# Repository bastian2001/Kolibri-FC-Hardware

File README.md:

# RP2350 Flight Controller for FPV

This is the hardware part of the Kolibri Flight Controller. Currently there are two versions: A 30mm (V0.5) and a 20mm (V0.6) FC. They are both pretty similar in terms of features, and mostly differ in their form factor and ease of soldering, but also featurewise, they are slightly different. They both feature:

-   3-8S input voltage
-   RP2350 microcontroller
-   2.4GHz ELRS onboard
-   5V 2.5A, 10V 2.5A buck converters
-   Analog character based OSD similar to Betaflight/iNav
-   Barometer (STM LPS22HB)
-   Speaker driver up to VBat

They differ slightly:

-   Gyro: BMI270 (30mm), ICM-42688-P with separate LDO (20mm)
-   ELRS: Gemini with PA/LNA (30mm), only one antenna with no PA/LNA (20mm)
-   Blackbox: SD slot (30mm), 256MiB flash chip (20mm)
-   20mm has a switchable 10V rail, 30mm uses that pin for a current sensor

While the 30mm FC works really well, the 20mm FC is just ordered and completely untested. While most features are a size decision, I will probably phase out the BMI270 and switch over to the ICM-42688-P, and I'd count a switchable 10V rail as more important than a current sensor, so as long as a 2350 is used, I will probably do that in the future, too. An RP235xB (only feasible on 30mm FC) has more pins though and might offer more features down the line, too.

The firmware and configurator can be found [here](https://github.com/bastian2001/Kolibri-FC).

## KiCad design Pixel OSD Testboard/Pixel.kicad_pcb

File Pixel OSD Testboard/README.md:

# Goal of this board

I want to implement a pixel OSD in some future FC version. Because I am very unsure about how PAL/NTSC work, I want to test all of the hardware on a separate, cheap and easily debuggable, board first. It has a bunch of components that I want to remove later on, and that are just for debugging (thus making it larger than it needs to be). Furthermore, some of the hardware is chosen purely because I have it laying around (e.g. RP2040 instead of RP2350), so I get rid of old stock.

Pixel OSD will have multiple advantages

-   Drawing graphs and free shapes
-   varying font size and grid
-   cheaper
-   shades of grey (hopefully)
-   optional: remove grey, save one pin compared to MAX (hopefully)

This board is only a proof of concept. I'll try to put it into my quad during flight, but in the end it will be implemented on the main FC. Thus, it will likely only support a character based OSD, so it doesn't require a whole rewrite of the FC firmware for now: The interface is Serial/UART with MSP Displayport. Yes, hopefully this can give us a higher character count on regular analog video (to some extent, because the resolution is already close to its limit)

## Stuff that will be removed later on

-   Maybe I can buffer a bit less: 1-2 op amp channels could go?
-   Are all 100nF caps needed?
-   video LPF on LM1881 input?
-   Virtual white and the white selector: White should just come from the peak detector
-   Some components for lines like VSync: I want to use only composite sync
-   RP2040/LDO/LED/USB: Will be integrated into main RP2350 instead of MAX7456E

## How it works

How the hardware works is commented on the sheet.

The software will use PIO to detect sync pulses, then use DMA to feed a pixel buffer into the PIO which then outputs the data, timed correctly. PIO has the advantage of not needing super precise interrupt timing, because the coprocessor is very precise time-wise by definition.

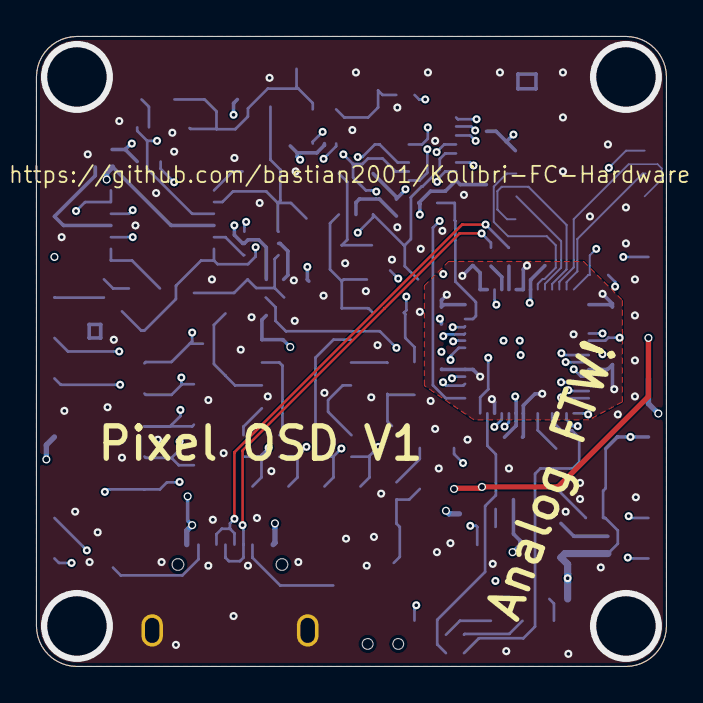
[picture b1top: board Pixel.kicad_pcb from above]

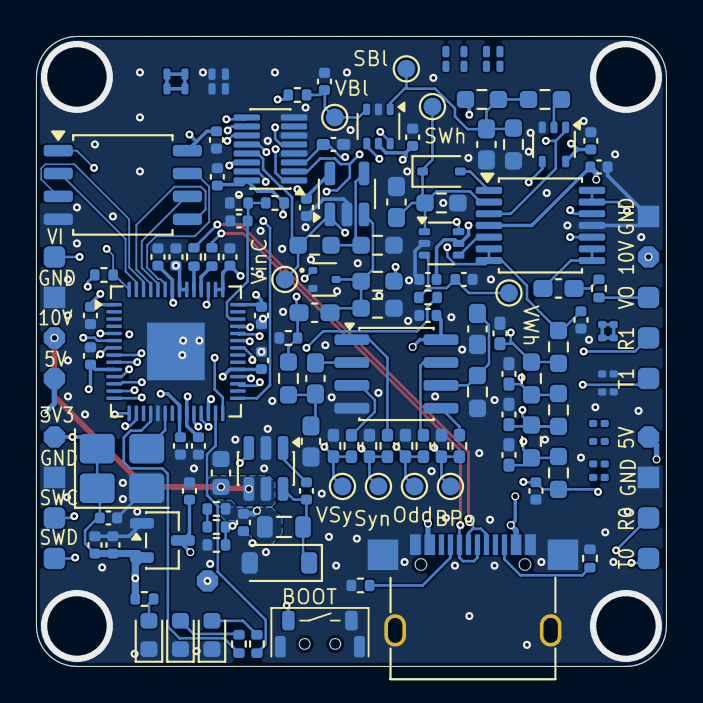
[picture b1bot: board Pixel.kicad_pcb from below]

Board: 6 copper layers, 35.0 x 35.0 mm, 145 parts (145 on the bottom side), 79 nets.

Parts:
C1, C2, C3, C4, C5, C6, C7, C8, C9, C10, C14, C15, C16, C19, C20, C22, C28, C45, C46, C54, C56, C57: 100n; C_0402_1005Metric
C11, C12: 100n; C_0603_1608Metric_Pad1.08x0.95mm_HandSolder
C13: 510p; C_0603_1608Metric_Pad1.08x0.95mm_HandSolder
C17, C18, C52: 10u; C_0603_1608Metric_Pad1.08x0.95mm_HandSolder
C21, C49, C50, C55: 1u; C_0402_1005Metric
C23: 10p; C_0402_1005Metric_Pad0.74x0.62mm_HandSolder
C24, C25, C26, C27: 100n; C_0402_1005Metric_Pad0.74x0.62mm_HandSolder
C29, C30, C31, C32, C33, C34, C35, C36: C; C_0201_0603Metric
C37, C38, C39, C40, C41, C42, C43, C44: C; C_0201_0603Metric_Pad0.64x0.40mm_HandSolder
C47, C51: 10u; C_0402_1005Metric
C48: 10u; C_0603_1608Metric
C53: 1u; C_0603_1608Metric_Pad1.08x0.95mm_HandSolder
D1: 1N4148WS; D_SOD-323
D2: yellow; LED_0603_1608Metric
D3: green; LED_0603_1608Metric
D4: red; LED_0603_1608Metric
D5: SL16; D_SOD-123
J1: USB_C_Receptacle_USB2.0_16P; USB-C SMD+THT
L1: 10u; L_0805_2012Metric
P1, P2, P3, P4, P5, P6, P7, P8: Solder_Pad_rounded
P9, P10, P11, P12, P13, P14: Solder_Pad_octa
P15, P16, P17, P18: Solder_Pad_rect
Q1: 2SK3019; SOT-523
R1, R2: 5.1k; R_0402_1005Metric
R3, R4: 27; R_0402_1005Metric
R5: 680; R_0603_1608Metric_Pad0.98x0.95mm_HandSolder
R6: 620; R_0603_1608Metric_Pad0.98x0.95mm_HandSolder
R7, R9, R11, R13: 33k; R_0402_1005Metric_Pad0.72x0.64mm_HandSolder
R8, R10, R12, R14: 100k; R_0402_1005Metric_Pad0.72x0.64mm_HandSolder
R15, R39: 1k; R_0402_1005Metric
R16, R27, R36: 10k; R_0402_1005Metric
R18: 100; R_0603_1608Metric_Pad0.98x0.95mm_HandSolder
R19, R20: 100k; R_0603_1608Metric_Pad0.98x0.95mm_HandSolder
R22, R23, R24, R25, R26, R43, R44: 1k; R_0603_1608Metric_Pad0.98x0.95mm_HandSolder
R28, R29: 75; R_0402_1005Metric
R32, R33: 100k; R_0402_1005Metric
R34: 47k; R_0402_1005Metric
R35: 15k; R_0402_1005Metric
R37, R38: 470; R_0402_1005Metric
R40: 1M; R_0603_1608Metric_Pad0.98x0.95mm_HandSolder
R41: 2.2M; R_0603_1608Metric_Pad0.98x0.95mm_HandSolder
R42: 390k; R_0603_1608Metric_Pad0.98x0.95mm_HandSolder
SW1: Button C530669
TP1, TP2, TP3, TP4, TP5, TP6, TP8, TP9, TP10: TestPoint_Probe; TestPoint_Pad_D1.0mm
U1: RP2040; QFN-56-1EP_7x7mm_P0.4mm_EP3.2x3.2mm
U2: LM1881; SOIC-8_3.9x4.9mm_P1.27mm
U3: W25Q16JVSS; SOIC-8_5.3x5.3mm_P1.27mm
U4: Opamp_Quad; TSSOP-14_4.4x5mm_P0.65mm
U5: 74LVC1G66; SOT-353_SC-70-5
U6, U10: FSA3157P6X; SOT-363_SC-70-6
U7: TMUX1308DYY; Texas_DYY0016A_TSOT-23-16_2x4.2mm_P0.5mm
U8: LGS5145; SOT-23-6
U9: C19631737; SOT-23-3
U11: OPA188xxDBV; TSOT-23-5
Y1: ASE-xxxMHz; Oscillator_SMD_Abracon_ASE-4Pin_3.2x2.5mm_HandSoldering

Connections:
+1V1: C8.1, C9.1, U1.23 (DVDD), U1.45 (VREG_VOUT), U1.50 (DVDD)
+3V3: C1.1, C2.1, C3.1, C4.1, C5.1, C6.1, C7.1, C10.1, C15.1, C22.1, C45.1, C50.1, C51.1, C56.1, C57.1, P9.1, P11.1, R32.1, R39.1, R40.1, R41.1, U1.1 (IOVDD), U1.10 (IOVDD), U1.22 (IOVDD), U1.26 (RUN), U1.33 (IOVDD), U1.42 (IOVDD), U1.43 (ADC_AVDD), U1.44 (VREG_IN), U1.48 (USB_VDD), U1.49 (IOVDD), U3.8 (VCC), U5.5 (VCC), U6.5 (V+), U7.16 (V_{CC}), U9.2 (VO), U10.5 (V+), Y1.1 (EN), Y1.4 (Vdd)
+5V: C14.1, C16.1, C47.1, C49.1, C54.1, J1.A4 (VBUS), J1.A9 (VBUS), J1.B4 (VBUS), J1.B9 (VBUS), L1.2, P10.1, P12.1, R34.1, U2.8 (VCC), U4.4 (V+), U9.3 (VI), U11.5 (V+)
+10V: C48.1, P13.1, P14.1, U8.4 (EN), U8.5 (VIN)
/BACK_PORCH: R11.2, R12.1, TP3.1, U1.13 (GPIO10)
/BLACK_ADC: C19.1, R26.2, U1.39 (GPIO27_ADC1), U4.13 (-), U4.14, U7.14 (Y1)
/BLACK_CHG: U1.12 (GPIO9), U5.4
/BLACK_SAH: C18.1, R18.2, R20.1, R40.2, TP8.1, U10.1
/BLACK_SELECT: U1.28 (GPIO17), U10.6
/COMPOSITE_SYNC: R7.2, R8.1, TP1.1, U1.5 (GPIO3)
/GREY1: C27.1, R25.2, R26.1, U7.15 (Y2)
/GREY2: C26.1, R24.2, R25.1, U7.12 (Y3)
/GREY3: C25.1, R23.2, R24.1, U7.1 (Y4)
/GREY4: C24.1, R22.2, R23.1, U7.5 (Y5)
/LED1: R38.1, U1.27 (GPIO16)
/LED2: R37.1, U1.18 (GPIO15)
/ODD_FRAME: R13.2, R14.1, TP4.1, U1.7 (GPIO5)
/RX0: P4.1, U1.16 (GPIO13)
/RX1: P8.1, U1.32 (GPIO21)
/SWCLK: P5.1, U1.24 (SWCLK)
/SWDIO: P6.1, U1.25 (SWD)
/SYNC_CLAMP: Q1.1 (G), U1.14 (GPIO11)
/TEST_ADC: C28.1, R32.2, R33.1, U1.40 (GPIO28_ADC2)
/TX0: P3.1, U1.15 (GPIO12)
/TX1: P7.1, U1.31 (GPIO20)
/USBD+: R4.2, U1.47 (USB_DP)
/USBD-: R3.2, U1.46 (USB_DM)
/VBLACK_PWM: R16.1, U1.29 (GPIO18)
/VIDEO_IN: C53.1, P1.1, R6.1, R28.1
/VIDEO_IN_CLAMP: R43.1, TP9.1, U4.3 (+), U5.1, U7.13 (Y0), U11.1
/VIDEO_OUT: P2.1, R29.2
/VSEL0: U1.8 (GPIO6), U7.11 (S0)
/VSEL1: U1.9 (GPIO7), U7.10 (S1)
/VSEL2: U1.11 (GPIO8), U7.9 (S2)
/VSYNC: R9.2, R10.1, TP2.1, U1.6 (GPIO4)
/VWHITE_PWM: R27.1, U1.36 (GPIO24)
/WHITE_ADC: C20.1, R22.1, U1.38 (GPIO26_ADC0), U4.6 (-), U4.7, U7.2 (Y6)
/WHITE_SAH: C17.1, D1.1 (K), R19.1, TP5.1, U4.2 (-), U6.1
/WHITE_SELECT: U1.37 (GPIO25), U6.6
GND: C1.2, C2.2, C3.2, C4.2, C5.2, C6.2, C7.2, C8.2, C9.2, C10.2, C11.2, C13.1, C14.2, C15.2, C16.2, C17.2, C18.2, C19.2, C20.2, C21.2, C22.2, C23.2, C24.2, C25.2, C26.2, C27.2, C28.2, C33.1, C33.2, C34.1, C34.2, C41.1, C41.2, C42.1, C42.2, C45.2, C47.2, C48.2, C49.2, C50.2, C51.2, C54.2, C55.2, C56.2, C57.2, D2.1 (K), D3.1 (K), D4.1 (K), D5.2 (A), J1.A1 (GND), J1.A12 (GND), J1.B1 (GND), J1.B12 (GND), J1.S1 (SHIELD), P15.1, P16.1, P17.1, P18.1, Q1.2 (S), R1.2, R2.2, R5.2, R8.2, R10.2, R12.2, R14.2, R19.2, R20.2, R28.2, R33.2, R36.2, R42.2, R44.2, SW1.2, SW1.3 (MP), SW1.4 (MP), U1.19 (TESTEN), U1.57 (GND), U2.4 (GND), U3.4 (GND), U4.11 (V-), U5.3 (GND), U6.2 (GND), U7.4 (Y7), U7.6 (~E), U7.8 (GND), U8.2 (GND), U9.1 (GND), U10.2 (GND), U11.2 (V-), Y1.2 (GND)
unnamed: C12.1, C13.2, R6.2
unnamed: C21.1, R27.2, TP6.1, U6.3
unnamed: C35.1, C35.2, C36.1, C36.2
unnamed: C43.1, C43.2, C44.1, C44.2
unnamed: C52.2, R29.1
unnamed: C55.1, R16.2, TP10.1, U10.3
unnamed: D1.2 (A), U4.1
unnamed: D2.2 (A), R38.2
unnamed: D3.2 (A), R37.2
unnamed: D4.2 (A), R39.2
unnamed: C46.1, D5.1 (K), L1.1, U8.6 (SW)
unnamed: J1.A5 (CC1), R1.1
unnamed: J1.B5 (CC2), R2.1
unnamed: J1.A6 (D+), J1.B6 (D+), R4.1
unnamed: J1.A7 (D-), J1.B7 (D-), R3.1
unnamed: C53.2, Q1.3 (D), R41.2, R42.1, U11.3 (+)
unnamed: R15.1, SW1.1
unnamed: R18.1, U5.2
unnamed: R34.2, R35.1
unnamed: U1.52 (QSPI_SCLK), U3.6 (CLK)
unnamed: U1.53 (QSPI_SD0), U3.5 (DI/IO_{0})
unnamed: U1.55 (QSPI_SD1), U3.2 (DO/IO_{1})
unnamed: U1.54 (QSPI_SD2), U3.3 (~WP/IO_{2})
unnamed: U1.51 (QSPI_SD3), U3.7 (~HOLD/~RESET/IO_{3})
unnamed: R15.2, U1.56 (QSPI_SS), U3.1 (~CS)
unnamed: U1.20 (XIN), Y1.3 (OUT)
unnamed: R11.1, U2.5 (BPOUT)
unnamed: R7.1, U2.1 (CSOUT)
unnamed: C12.2, U2.2 (CVIN)
unnamed: R13.1, U2.7 (OEOUT)
unnamed: C11.1, R5.1, U2.6 (RSET)
unnamed: R9.1, U2.3 (VSOUT)
unnamed: U4.5 (+), U6.4
unnamed: C23.1, U4.10 (+), U7.3 (Z)
unnamed: C52.1, U4.8, U4.9 (-)
unnamed: U4.12 (+), U10.4
unnamed: C46.2, U8.1 (BST)
unnamed: R35.2, R36.1, U8.3 (FB)
unnamed: R43.2, R44.1, U11.4 (-)

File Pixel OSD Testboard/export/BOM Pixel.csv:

#,Reference,Value,Footprint,Qty
1,'C1,C2,C3,C4,C5,C6,C7,C8,C9,C10,C14,C15,C16,C19,C20,C22,C28,C45,C46,C54,C56,C57',100n,Capacitor_SMD:C_0402_1005Metric,22
2,'C11,C12',100n,Capacitor_SMD:C_0603_1608Metric_Pad1.08x0.95mm_HandSolder,2
3,C13,510p,Capacitor_SMD:C_0603_1608Metric_Pad1.08x0.95mm_HandSolder,1
4,'C17,C18,C52',10u,Capacitor_SMD:C_0603_1608Metric_Pad1.08x0.95mm_HandSolder,3
5,'C21,C49,C50,C55',1u,Capacitor_SMD:C_0402_1005Metric,4
6,C23,10p,Capacitor_SMD:C_0402_1005Metric_Pad0.74x0.62mm_HandSolder,1
7,'C24,C25,C26,C27',100n,Capacitor_SMD:C_0402_1005Metric_Pad0.74x0.62mm_HandSolder,4
8,'C29,C30,C31,C32,C33,C34,C35,C36',C,Capacitor_SMD:C_0201_0603Metric,8
9,'C37,C38,C39,C40,C41,C42,C43,C44',C,Capacitor_SMD:C_0201_0603Metric_Pad0.64x0.40mm_HandSolder,8
10,'C47,C51',10u,Capacitor_SMD:C_0402_1005Metric,2
11,C48,10u,Capacitor_SMD:C_0603_1608Metric,1
12,C53,1u,Capacitor_SMD:C_0603_1608Metric_Pad1.08x0.95mm_HandSolder,1
13,D1,1N4148WS,Diode_SMD:D_SOD-323,1
14,D2,yellow,LED_SMD:LED_0603_1608Metric,1
15,D3,green,LED_SMD:LED_0603_1608Metric,1
16,D4,red,LED_SMD:LED_0603_1608Metric,1
17,D5,SL16,Diode_SMD:D_SOD-123,1
18,J1,USB_C_Receptacle_USB2.0_16P,Kolibri custom:USB-C SMD+THT,1
19,L1,10u,Inductor_SMD:L_0805_2012Metric,1
20,'P1,P2,P3,P4,P5,P6,P7,P8',~,Kolibri custom:Solder_Pad_rounded,8
21,'P9,P10,P11,P12,P13,P14',~,Kolibri custom:Solder_Pad_octa,6
22,'P15,P16,P17,P18',~,Kolibri custom:Solder_Pad_rect,4
23,Q1,2SK3019,Package_TO_SOT_SMD:SOT-523,1
24,'R1,R2',5.1k,Resistor_SMD:R_0402_1005Metric,2
25,'R3,R4',27,Resistor_SMD:R_0402_1005Metric,2
26,R5,680,Resistor_SMD:R_0603_1608Metric_Pad0.98x0.95mm_HandSolder,1
27,R6,620,Resistor_SMD:R_0603_1608Metric_Pad0.98x0.95mm_HandSolder,1
28,'R7,R9,R11,R13',33k,Resistor_SMD:R_0402_1005Metric_Pad0.72x0.64mm_HandSolder,4
29,'R8,R10,R12,R14',100k,Resistor_SMD:R_0402_1005Metric_Pad0.72x0.64mm_HandSolder,4
30,'R15,R39',1k,Resistor_SMD:R_0402_1005Metric,2
31,'R16,R27,R36',10k,Resistor_SMD:R_0402_1005Metric,3
32,R18,100,Resistor_SMD:R_0603_1608Metric_Pad0.98x0.95mm_HandSolder,1
33,'R19,R20',100k,Resistor_SMD:R_0603_1608Metric_Pad0.98x0.95mm_HandSolder,2
34,'R22,R23,R24,R25,R26,R43,R44',1k,Resistor_SMD:R_0603_1608Metric_Pad0.98x0.95mm_HandSolder,7
35,'R28,R29',75,Resistor_SMD:R_0402_1005Metric,2
36,'R32,R33',100k,Resistor_SMD:R_0402_1005Metric,2
37,R34,47k,Resistor_SMD:R_0402_1005Metric,1
38,R35,15k,Resistor_SMD:R_0402_1005Metric,1
39,'R37,R38',470,Resistor_SMD:R_0402_1005Metric,2
40,R40,1M,Resistor_SMD:R_0603_1608Metric_Pad0.98x0.95mm_HandSolder,1
41,R41,2.2M,Resistor_SMD:R_0603_1608Metric_Pad0.98x0.95mm_HandSolder,1
42,R42,390k,Resistor_SMD:R_0603_1608Metric_Pad0.98x0.95mm_HandSolder,1
43,SW1,~,Kolibri custom:Button C530669,1
44,'TP1,TP2,TP3,TP4,TP5,TP6,TP8,TP9,TP10',TestPoint_Probe,TestPoint:TestPoint_Pad_D1.0mm,9
45,U1,RP2040,Package_DFN_QFN:QFN-56-1EP_7x7mm_P0.4mm_EP3.2x3.2mm,1
46,U2,LM1881,Package_SO:SOIC-8_3.9x4.9mm_P1.27mm,1
47,U3,W25Q16JVSS,Package_SO:SOIC-8_5.3x5.3mm_P1.27mm,1
48,U4,Opamp_Quad,Package_SO:TSSOP-14_4.4x5mm_P0.65mm,1
49,U5,74LVC1G66,Package_TO_SOT_SMD:SOT-353_SC-70-5,1
50,'U6,U10',FSA3157P6X,Package_TO_SOT_SMD:SOT-363_SC-70-6,2
51,U7,TMUX1308DYY,Package_SO:Texas_DYY0016A_TSOT-23-16_2x4.2mm_P0.5mm,1
52,U8,LGS5145,Package_TO_SOT_SMD:SOT-23-6,1
53,U9,C19631737,Package_TO_SOT_SMD:SOT-23-3,1
54,U11,OPA188xxDBV,Package_TO_SOT_SMD:TSOT-23-5,1
55,Y1,ASE-xxxMHz,Oscillator:Oscillator_SMD_Abracon_ASE-4Pin_3.2x2.5mm_HandSoldering,1

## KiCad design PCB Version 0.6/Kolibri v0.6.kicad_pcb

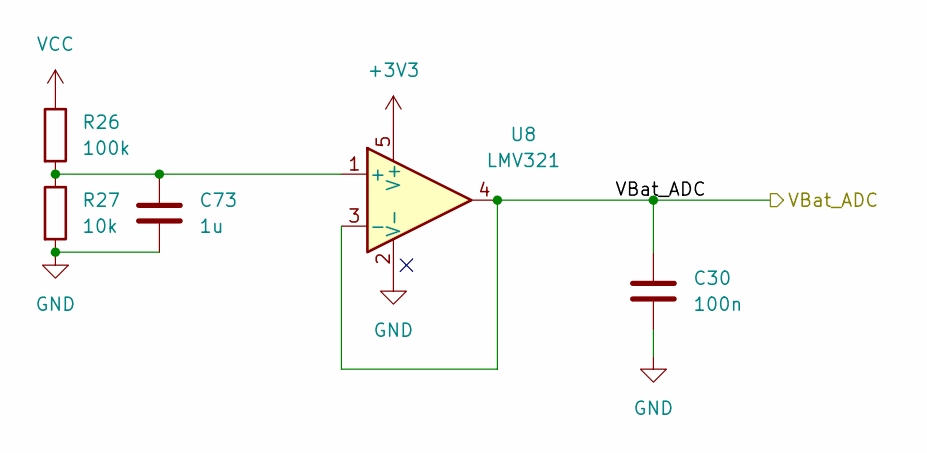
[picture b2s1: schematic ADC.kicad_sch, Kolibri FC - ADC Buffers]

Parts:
C30: 100n; C_0402_1005Metric
C73: 1u; C_0402_1005Metric
R26: 100k; R_0402_1005Metric
R27: 10k; R_0402_1005Metric
U8: LMV321; SOT-353_SC-70-5

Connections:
+3V3: U8.5 (V+); also elsewhere on the board
/ADC/VBat_ADC: C30.1, U8.3 (-), U8.4; also elsewhere on the board
GND: C30.2, C73.1, R27.2, U8.2 (V-); also elsewhere on the board
unnamed: C73.2, R26.2, R27.1, U8.1 (+)
VCC: R26.1; also elsewhere on the board

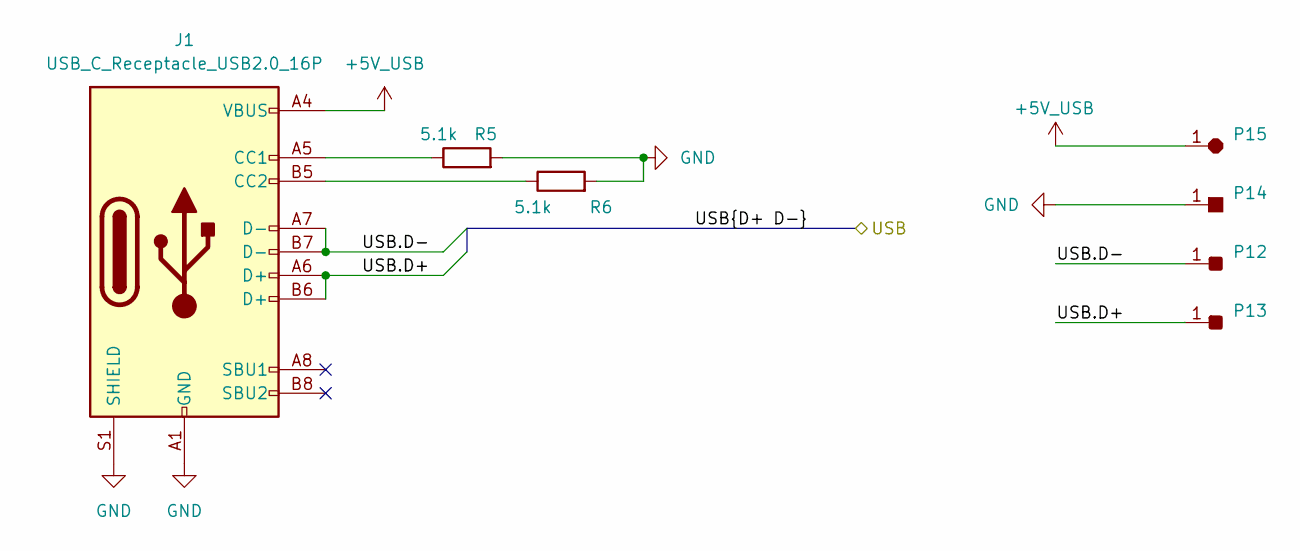
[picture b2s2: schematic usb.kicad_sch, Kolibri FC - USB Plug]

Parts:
J1: USB_C_Receptacle_USB2.0_16P; USB-C SMD+THT
P12, P13: Solder_Pad_rounded
P14: Solder_Pad_rect
P15: Solder_Pad_octa
R5, R6: 5.1k; R_0402_1005Metric

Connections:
+5V_USB: J1.A4 (VBUS), J1.A9 (VBUS), J1.B4 (VBUS), J1.B9 (VBUS), P15.1; also elsewhere on the board
/USB.D+: J1.A6 (D+), J1.B6 (D+), P13.1; also elsewhere on the board
/USB.D-: J1.A7 (D-), J1.B7 (D-), P12.1; also elsewhere on the board
GND: J1.A1 (GND), J1.A12 (GND), J1.B1 (GND), J1.B12 (GND), J1.S1 (SHIELD), P14.1, R5.2, R6.2; also elsewhere on the board
unnamed: J1.A5 (CC1), R5.1
unnamed: J1.B5 (CC2), R6.1

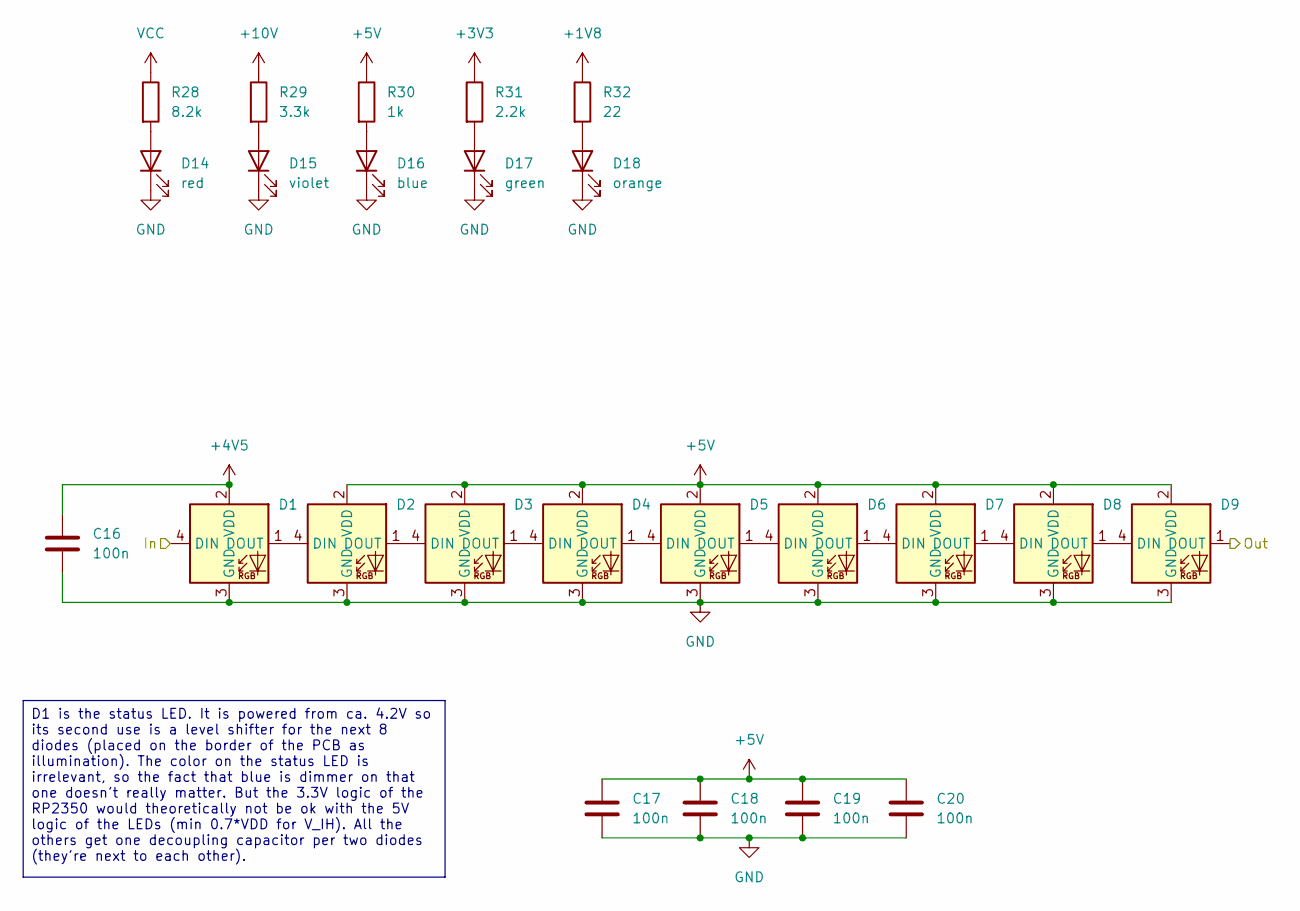
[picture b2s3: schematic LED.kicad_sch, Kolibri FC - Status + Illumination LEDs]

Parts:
C16, C17, C18, C19, C20: 100n; C_0402_1005Metric
D1, D2, D3, D4, D5, D6, D7, D8, D9: WS2812B_1615
D14: red; LED_0603_1608Metric
D15: violet; LED_0603_1608Metric
D16: blue; LED_0603_1608Metric
D17: green; LED_0603_1608Metric
D18: orange; LED_0603_1608Metric
R28: 8.2k; R_0402_1005Metric
R29: 3.3k; R_0402_1005Metric
R30: 1k; R_0402_1005Metric
R31: 2.2k; R_0402_1005Metric
R32: 22; R_0402_1005Metric

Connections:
+3V3: R31.1; also elsewhere on the board
+4V5: C16.1, D1.2 (VDD); also elsewhere on the board
+5V: C17.1, C18.1, C19.1, C20.1, D2.2 (VDD), D3.2 (VDD), D4.2 (VDD), D5.2 (VDD), D6.2 (VDD), D7.2 (VDD), D8.2 (VDD), D9.2 (VDD), R30.1; also elsewhere on the board
+10V: R29.1; also elsewhere on the board
/Connectors/LED: D9.1 (DOUT); also elsewhere on the board
/RP2350/LED: D1.4 (DIN); also elsewhere on the board
GND: C16.2, C17.2, C18.2, C19.2, C20.2, D1.3 (GND), D2.3 (GND), D3.3 (GND), D4.3 (GND), D5.3 (GND), D6.3 (GND), D7.3 (GND), D8.3 (GND), D9.3 (GND), D14.1 (K), D15.1 (K), D16.1 (K), D17.1 (K), D18.1 (K); also elsewhere on the board
unnamed: D1.1 (DOUT), D2.4 (DIN)
unnamed: D2.1 (DOUT), D3.4 (DIN)
unnamed: D3.1 (DOUT), D4.4 (DIN)
unnamed: D4.1 (DOUT), D5.4 (DIN)
unnamed: D5.1 (DOUT), D6.4 (DIN)
unnamed: D6.1 (DOUT), D7.4 (DIN)
unnamed: D7.1 (DOUT), D8.4 (DIN)
unnamed: D8.1 (DOUT), D9.4 (DIN)
unnamed: D14.2 (A), R28.2
unnamed: D15.2 (A), R29.2
unnamed: D16.2 (A), R30.2
unnamed: D17.2 (A), R31.2
unnamed: D18.2 (A), R32.2
VCC: R28.1; also elsewhere on the board

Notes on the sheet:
D1 is the status LED. It is powered from ca. 4.2V so its second use is a level shifter for the next 8 diodes (placed on the border of the PCB as illumination). The color on the status LED is irrelevant, so the fact that blue is dimmer on that one doesn't really matter. But the 3.3V logic of the RP2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

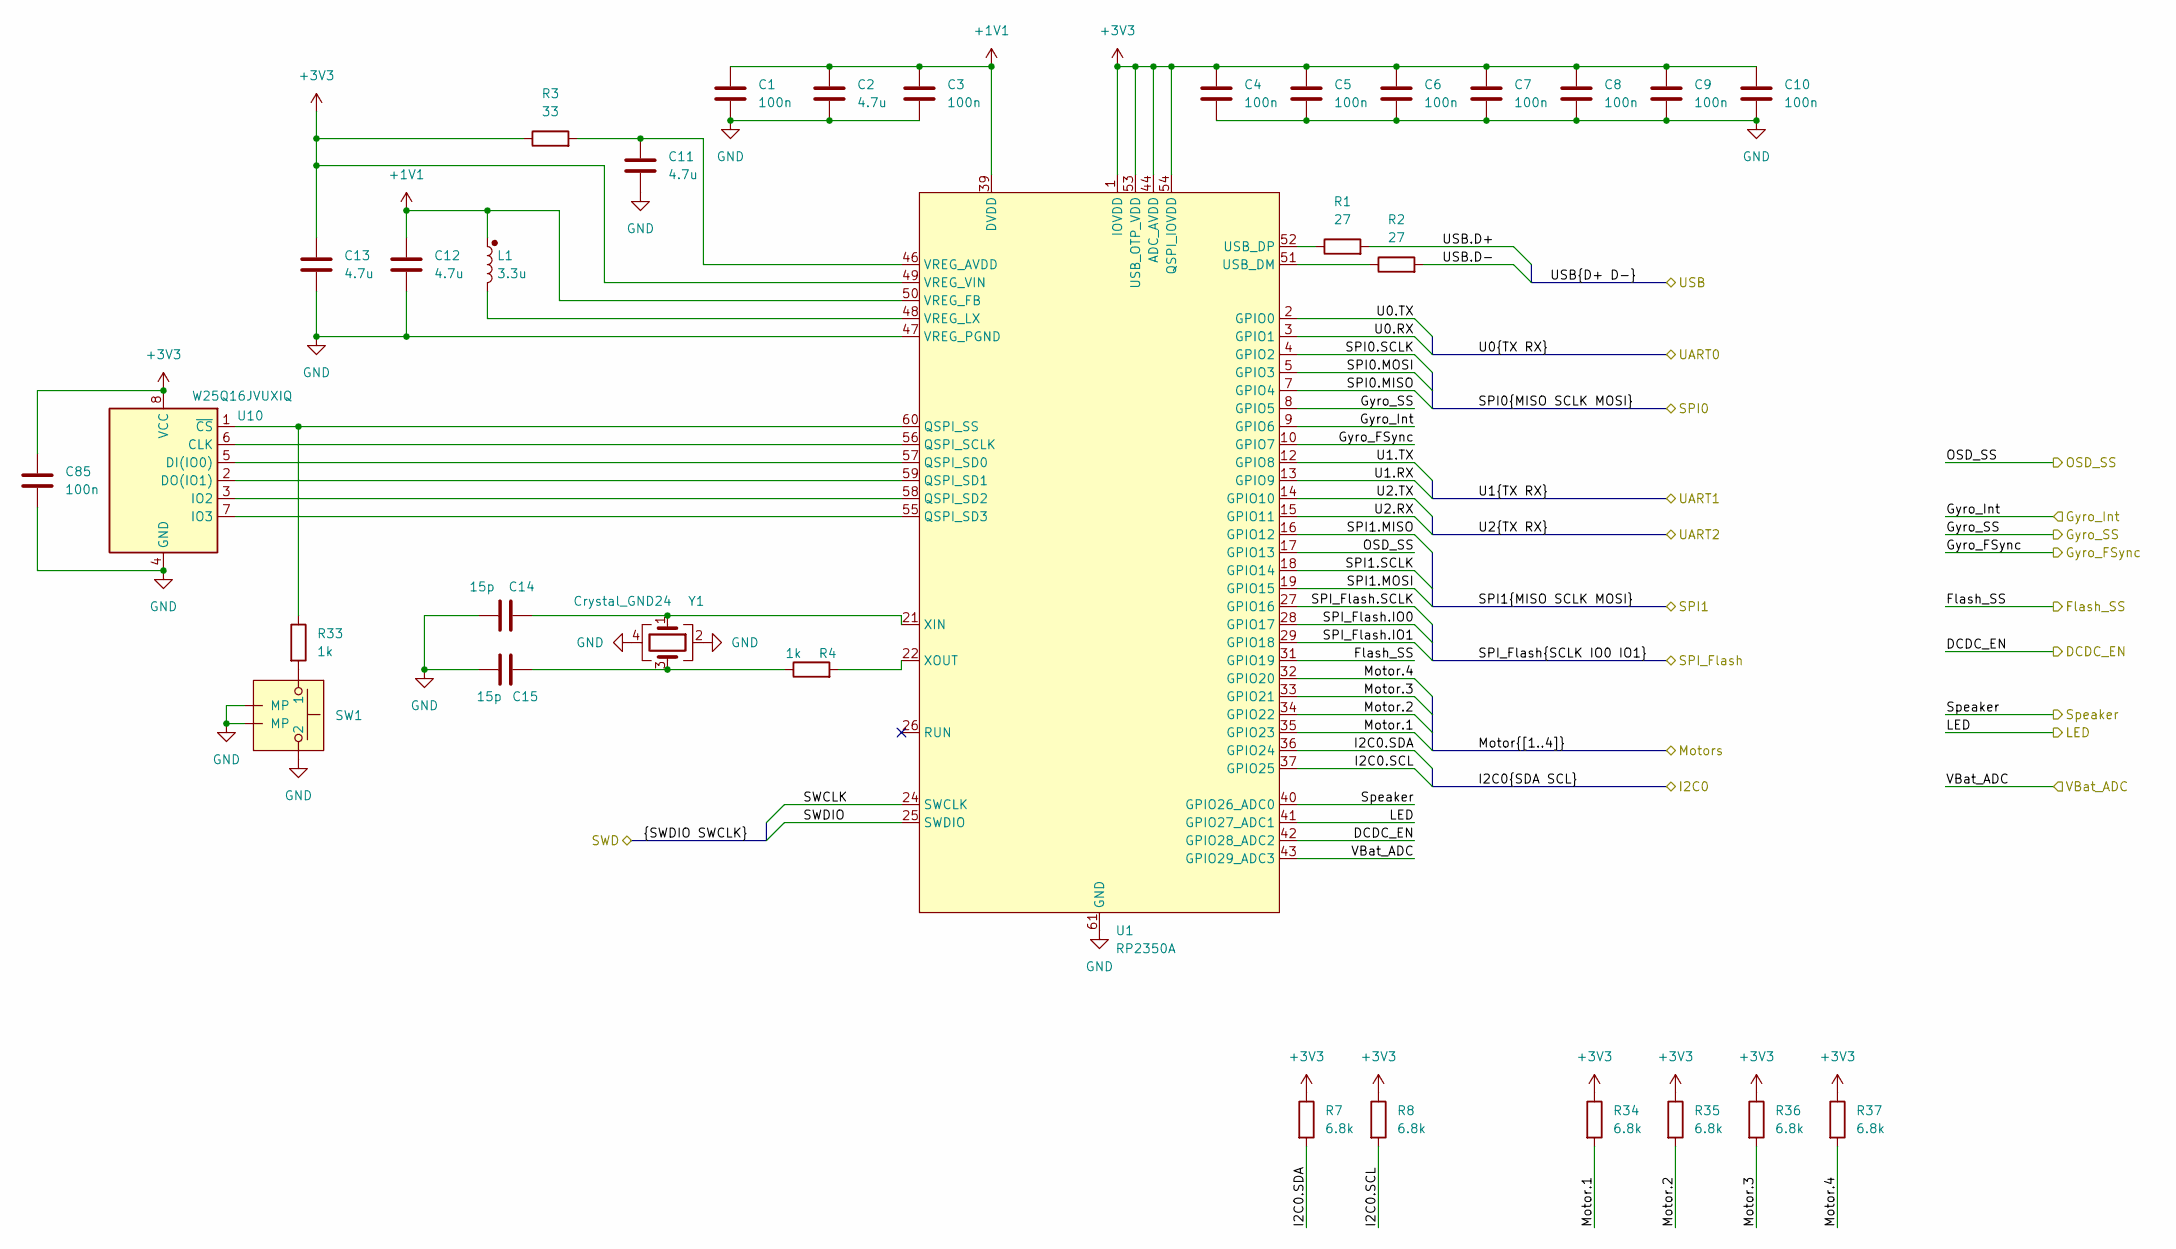
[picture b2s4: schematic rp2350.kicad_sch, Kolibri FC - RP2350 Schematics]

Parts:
C1, C3, C4, C5, C6, C7, C8, C9, C10: 100n; C_0402_1005Metric_Pad0.74x0.62mm_HandSolder
C2: 4.7u; C_0402_1005Metric_Pad0.74x0.62mm_HandSolder
C11, C12, C13: 4.7u; C_0402_1005Metric
C14, C15: 15p; C_0402_1005Metric_Pad0.74x0.62mm_HandSolder
C85: 100n; C_0402_1005Metric
L1: 3.3u; Abracon AOTA 0806
R1, R2: 27; R_0402_1005Metric
R3: 33; R_0402_1005Metric
R4, R33: 1k; R_0402_1005Metric_Pad0.72x0.64mm_HandSolder
R7, R8, R34, R35, R36, R37: 6.8k; R_0402_1005Metric_Pad0.72x0.64mm_HandSolder
SW1: Button C530669 wo holes
U1: RP2350A; QFN-60_EP_7x7_Pitch0.4mm
U10: W25Q16JVUXIQ; Winbond_USON-8-1EP_3x2mm_P0.5mm_EP0.2x1.6mm
Y1: Crystal_GND24; Crystal_SMD_2520-4Pin_2.5x2.0mm

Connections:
+1V1: C1.1, C2.1, C3.1, C12.1, L1.1, U1.6 (DVDD), U1.23 (DVDD), U1.39 (DVDD), U1.50 (VREG_FB)
+3V3: C4.1, C5.1, C6.1, C7.1, C8.1, C9.1, C10.1, C13.1, C85.1, R3.1, R7.1, R8.1, R34.1, R35.1, R36.1, R37.1, U1.1 (IOVDD), U1.11 (IOVDD), U1.20 (IOVDD), U1.30 (IOVDD), U1.38 (IOVDD), U1.44 (ADC_AVDD), U1.45 (IOVDD), U1.49 (VREG_VIN), U1.53 (USB_OTP_VDD), U1.54 (QSPI_IOVDD), U10.8 (VCC); also elsewhere on the board
/ADC/VBat_ADC: U1.43 (GPIO29_ADC3); also elsewhere on the board
/I2C0.SCL: R8.2, U1.37 (GPIO25); also elsewhere on the board
/I2C0.SDA: R7.2, U1.36 (GPIO24); also elsewhere on the board
/Motor.1: R34.2, U1.35 (GPIO23); also elsewhere on the board
/Motor.2: R35.2, U1.34 (GPIO22); also elsewhere on the board
/Motor.3: R36.2, U1.33 (GPIO21); also elsewhere on the board
/Motor.4: R37.2, U1.32 (GPIO20); also elsewhere on the board
/Power/DCDC_EN: U1.42 (GPIO28_ADC2); also elsewhere on the board
/RP2350/Flash_SS: U1.31 (GPIO19); also elsewhere on the board
/RP2350/Gyro_FSync: U1.10 (GPIO7); also elsewhere on the board
/RP2350/Gyro_Int: U1.9 (GPIO6); also elsewhere on the board
/RP2350/Gyro_SS: U1.8 (GPIO5); also elsewhere on the board
/RP2350/LED: U1.41 (GPIO27_ADC1); also elsewhere on the board
/RP2350/OSD_SS: U1.17 (GPIO13); also elsewhere on the board
/RP2350/Speaker: U1.40 (GPIO26_ADC0); also elsewhere on the board
/SPI0.MISO: U1.7 (GPIO4); also elsewhere on the board
/SPI0.MOSI: U1.5 (GPIO3); also elsewhere on the board
/SPI0.SCLK: U1.4 (GPIO2); also elsewhere on the board
/SPI1.MISO: U1.16 (GPIO12); also elsewhere on the board
/SPI1.MOSI: U1.19 (GPIO15); also elsewhere on the board
/SPI1.SCLK: U1.18 (GPIO14); also elsewhere on the board
/SPI_Flash.IO0: U1.28 (GPIO17); also elsewhere on the board
/SPI_Flash.IO1: U1.29 (GPIO18); also elsewhere on the board
/SPI_Flash.SCLK: U1.27 (GPIO16); also elsewhere on the board
/SWCLK: U1.24 (SWCLK); also elsewhere on the board
/SWDIO: U1.25 (SWDIO); also elsewhere on the board
/U0.RX: U1.3 (GPIO1); also elsewhere on the board
/U0.TX: U1.2 (GPIO0); also elsewhere on the board
/U1.RX: U1.13 (GPIO9); also elsewhere on the board
/U1.TX: U1.12 (GPIO8); also elsewhere on the board
/U2.RX: U1.15 (GPIO11); also elsewhere on the board
/U2.TX: U1.14 (GPIO10); also elsewhere on the board
/USB.D+: R1.2; also elsewhere on the board
/USB.D-: R2.2; also elsewhere on the board
GND: C1.2, C2.2, C3.2, C4.2, C5.2, C6.2, C7.2, C8.2, C9.2, C10.2, C11.2, C12.2, C13.2, C14.1, C15.1, C85.2, SW1.2, SW1.3 (MP), SW1.4 (MP), U1.47 (VREG_PGND), U1.61 (GND), U10.4 (GND), U10.9 (EP), Y1.2, Y1.4; also elsewhere on the board
unnamed: C15.2, R4.1, Y1.3
unnamed: R33.2, SW1.1
unnamed: U1.56 (QSPI_SCLK), U10.6 (CLK)
unnamed: U1.57 (QSPI_SD0), U10.5 (DI(IO0))
unnamed: U1.59 (QSPI_SD1), U10.2 (DO(IO1))
unnamed: U1.58 (QSPI_SD2), U10.3 (IO2)
unnamed: U1.55 (QSPI_SD3), U10.7 (IO3)
unnamed: R33.1, U1.60 (QSPI_SS), U10.1 (~CS)
unnamed: R2.1, U1.51 (USB_DM)
unnamed: R1.1, U1.52 (USB_DP)
unnamed: C11.1, R3.2, U1.46 (VREG_AVDD)
unnamed: L1.2, U1.48 (VREG_LX)
unnamed: C14.2, U1.21 (XIN), Y1.1
unnamed: R4.2, U1.22 (XOUT)

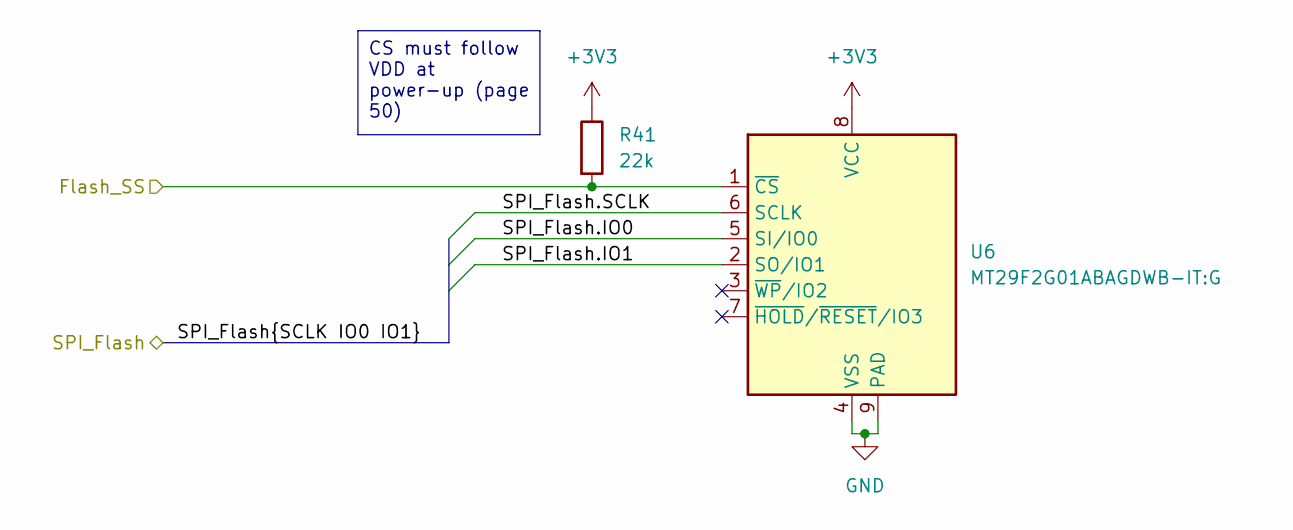
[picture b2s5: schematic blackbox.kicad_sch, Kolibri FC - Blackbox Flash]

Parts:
R41: 22k; R_0402_1005Metric
U6: MT29F2G01ABAGDWB-IT:G; WSON-8-1EP_8x6mm_P1.27mm_EP3.4x4.3mm

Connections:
+3V3: R41.1, U6.8 (VCC); also elsewhere on the board
/RP2350/Flash_SS: R41.2, U6.1 (~CS); also elsewhere on the board
/SPI_Flash.IO0: U6.5 (SI/IO0); also elsewhere on the board
/SPI_Flash.IO1: U6.2 (SO/IO1); also elsewhere on the board
/SPI_Flash.SCLK: U6.6 (SCLK); also elsewhere on the board
GND: U6.4 (VSS), U6.9 (PAD); also elsewhere on the board

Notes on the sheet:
CS must follow VDD at power-up (page 50)

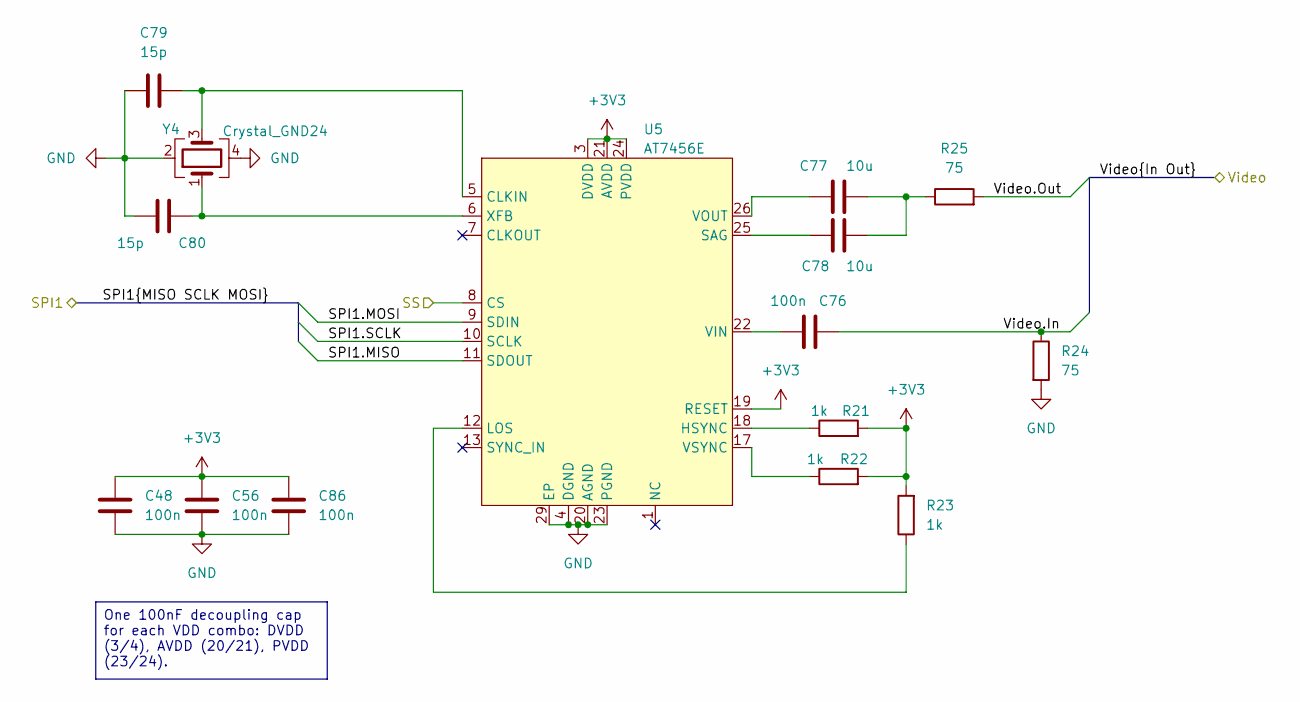
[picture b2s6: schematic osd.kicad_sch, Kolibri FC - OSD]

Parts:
C48, C76: 100n; C_0402_1005Metric
C56, C86: 100n; C_0402_1005Metric_Pad0.74x0.62mm_HandSolder
C77, C78: 10u; C_0402_1005Metric_Pad0.74x0.62mm_HandSolder
C79, C80: 15p; C_0402_1005Metric
R21, R22, R23: 1k; R_0402_1005Metric
R24: 75; R_0402_1005Metric
R25: 75; R_0402_1005Metric_Pad0.72x0.64mm_HandSolder
U5: AT7456E; HTSSOP-28-1EP_4.4x9.7mm_P0.65mm_EP2.75x6.2mm
Y4: Crystal_GND24; Crystal_SMD_2016-4Pin_2.0x1.6mm

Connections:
+3V3: C48.1, C56.1, C86.1, R21.2, R22.2, R23.2, U5.3 (DVDD), U5.19 (RESET), U5.21 (AVDD), U5.24 (PVDD); also elsewhere on the board
/RP2350/OSD_SS: U5.8 (CS); also elsewhere on the board
/SPI1.MISO: U5.11 (SDOUT); also elsewhere on the board
/SPI1.MOSI: U5.9 (SDIN); also elsewhere on the board
/SPI1.SCLK: U5.10 (SCLK); also elsewhere on the board
/Video.In: C76.2, R24.1; also elsewhere on the board
/Video.Out: R25.2; also elsewhere on the board
GND: C48.2, C56.2, C79.1, C80.2, C86.2, R24.2, U5.4 (DGND), U5.20 (AGND), U5.23 (PGND), U5.29 (EP), Y4.2, Y4.4; also elsewhere on the board
unnamed: C77.2, C78.1, R25.1
unnamed: C79.2, U5.5 (CLKIN), Y4.3
unnamed: R21.1, U5.18 (HSYNC)
unnamed: R23.1, U5.12 (LOS)
unnamed: C78.2, U5.25 (SAG)
unnamed: C76.1, U5.22 (VIN)
unnamed: R22.1, U5.17 (VSYNC)
unnamed: C80.1, U5.6 (XFB), Y4.1

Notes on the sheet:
One 100nF decoupling cap for each VDD combo: DVDD (3/4), AVDD (20/21), PVDD (23/24).

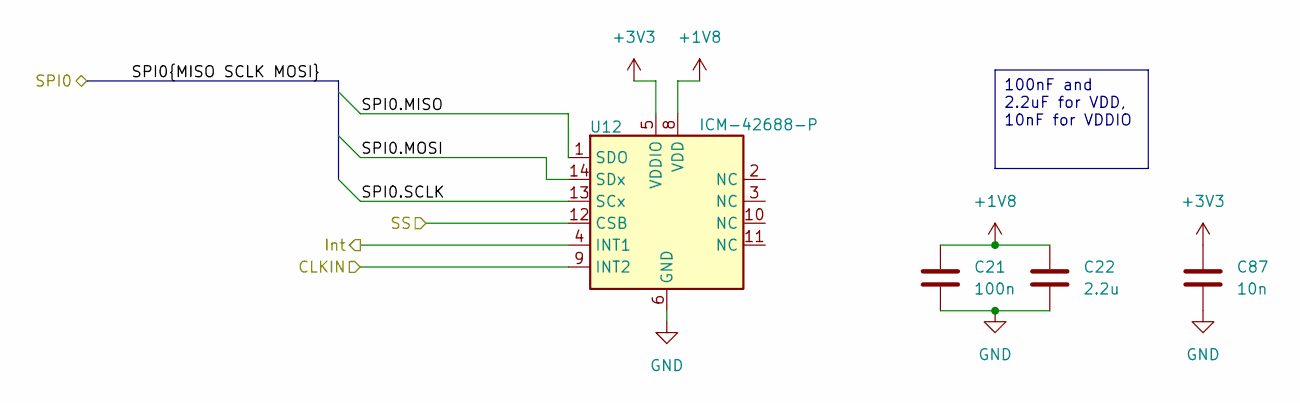
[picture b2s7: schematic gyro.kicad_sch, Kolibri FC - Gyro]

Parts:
C21: 100n; C_0402_1005Metric
C22: 2.2u; C_0402_1005Metric
C87: 10n; C_0402_1005Metric
U12: ICM-42688-P; LGA-14_3x2.5mm_P0.5mm_LayoutBorder3x4y

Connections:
+1V8: C21.1, C22.1, U12.8 (VDD); also elsewhere on the board
+3V3: C87.1, U12.5 (VDDIO); also elsewhere on the board
/RP2350/Gyro_FSync: U12.9 (INT2); also elsewhere on the board
/RP2350/Gyro_Int: U12.4 (INT1); also elsewhere on the board
/RP2350/Gyro_SS: U12.12 (CSB); also elsewhere on the board
/SPI0.MISO: U12.1 (SDO); also elsewhere on the board
/SPI0.MOSI: U12.14 (SDx); also elsewhere on the board
/SPI0.SCLK: U12.13 (SCx); also elsewhere on the board
GND: C21.2, C22.2, C87.2, U12.6 (GND), U12.7 (RES); also elsewhere on the board

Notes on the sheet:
100nF and 2.2uF for VDD, 10nF for VDDIO
